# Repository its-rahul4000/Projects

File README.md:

# 📂 Rahul Kumar – Engineering & Research Projects

This repository contains a collection of **academic, internship, research, and personal projects** developed during my undergraduate studies in **Electrical Engineering at IIT Bombay**.

The projects span across multiple domains:

- Cybersecurity
- Embedded Systems
- Artificial Intelligence & Machine Learning
- Full-Stack Development
- Computer Architecture
- Analog Computing
- Energy Systems & Forecasting
- Data Analytics

Each project includes code, reports, simulations, documentation, and real-world engineering solutions developed through academic, research, and industry experience.

# 📁 Project Overview

## 🛡️ Cybersecurity Log Intelligence System

### Enterprise Security Log Analysis & Threat Detection Platform

- Architected and developed an **enterprise Cybersecurity Log Intelligence System** for automated security log analysis and threat detection.
- Implemented **static rule-based and behavioral anomaly detection** to identify attacks from large-scale log datasets.
- Built an interactive **dashboard with visualizations**, PDF/CSV report generation, and automated security insights.
- Designed a secure **RBAC-based application** featuring Argon2id authentication, audit logging, configurable detection rules, concurrent log processing, and secure data lifecycle management.
- Incorporated industry security frameworks including **MITRE ATT&CK, OWASP, NIST SP 800-53, ISO/IEC 27001, CERT-In, and the EU Cyber Resilience Act**.

### Key Features

- Multi-format log parsing and automated threat detection
- Static signature and behavioral anomaly detection
- Interactive Streamlit dashboard with security analytics
- PDF & CSV security report generation
- Configurable detection-rule management
- Role-Based Access Control (Administrator & IT Owner)
- Audit logging and secure session management
- Concurrent processing for large log files

### Technologies

- Python
- Streamlit
- SQLite
- Pandas
- Plotly
- Argon2id Authentication
- YAML Rule Engine
- MITRE ATT&CK
- OWASP

## 🏗️ Concrete Maturity Meter

### Embedded IoT System for Concrete Strength Monitoring

- Developed a **low-power embedded device** for real-time monitoring of concrete curing using temperature-based maturity models.  
- Implemented **on-device computation of maturity index and strength %** using MCU.  
- Integrated **TMP1075 sensor, SPI Flash, and BLE (CC2650)** for sensing, storage, and communication.  
- Designed a **battery-powered ultra-low power system** using sleep modes and duty-cycled BLE.  
- Enables **non-destructive, in-situ strength estimation**, eliminating traditional delays.  

### Key Highlights

- Sampling every **10–15 minutes with long battery life (>2 months)**  
- Reliable BLE communication **through concrete (≈ 8–9 cm range)** 
- Compact embedded system (~40×30×20 mm)  
- Full pipeline: sensing → storage → computation → wireless broadcast  

## 🌊 Forecasting of Offshore Wind Power

### Time-Series Forecasting & Renewable Energy Analysis

- Developed a **data-driven forecasting model** for offshore wind power generation.  
- Applied **time-series analysis and machine learning techniques** to predict power output.  
- Preprocessed real-world datasets including **wind speed, temporal patterns, and environmental factors**.  
- Built models to capture **seasonal trends, variability, and uncertainty in renewable energy systems**.  

### Key Contributions

- Data cleaning and feature engineering for time-series modeling  
- Implementation of forecasting models (statistical / ML-based)  
- Performance evaluation using error metrics (MAE, RMSE)  
- Visualization of predicted vs actual wind power trends  

### Impact

- Helps in **grid stability and energy planning**  
- Supports **renewable energy integration**

## 🧠 Integrated AI Query System

### AI-powered Knowledge Assistant

- Built an AI system capable of **answering, comparing, and summarizing queries**.  
- Used **Sentence Transformers (semantic search)** + rule-based parsing.  
- Implemented complete pipeline for:
  - Data cleaning  
  - Entity resolution  
  - Insight extraction  
- Developed interactive UI using **Streamlit**.

## 🌐 Full Stack Website Development

### Full-Stack Hardware Store Website

- Built a **complete e-commerce platform** with separate **user & admin portals**.  
- Backend: **Node.js, Express.js, MongoDB**  
- Frontend: **HTML, CSS, JavaScript (responsive design)**  

### Features

- Product browsing + **Featured & Hot Products**
- Cart & order system  
- Admin dashboard (products, orders, messages)  
- Customer–admin communication  

## 💻 Pipelined CPU

### 5-Stage Pipelined Processor (VHDL)

- Designed an **8-bit pipelined CPU** with:
  - IF, ID, EX, MEM, WB stages  
- Implemented:
  - Hazard detection  
  - Data forwarding  
  - Pipeline stalls  

## 🧮 Multicycle CPU

### 16-bit Multicycle Processor

- Designed CPU using **FSM-controlled datapath architecture**  
- Supported:
  - Arithmetic operations  
  - Branching  
  - Memory access  

## 🔌 Microcontrollers UART Communication

### 8051 Communication System

- Implemented **master-slave communication** using AT89C5131  
- Designed **full-duplex UART logic** with synchronization  
- Displayed outputs on **LCD modules**  

## 📡 Wireless Communication (GNU Radio)

- Designed a **complete digital communication system** using GNU Radio  
- Implemented:
  - ASK, FSK, PSK, QAM  
- Tested with **RTL-SDR hardware**  
- Analyzed performance under noise and synchronization errors

 ## 🧪 VHDL Project

### Digital Logic Design

- Designed multiple components:
  - ALU  
  - FSM  
  - Multiplexers  
  - Adders  

- Implemented on FPGA with timing validation   
## ⚡ Analog Computer

### Vertical Motion Analog Computing System

- Designed an **analog computer using op-amps** to solve differential equations.  
- Implemented **integrators, summers, buffers** for physical system modeling.  
- Simulated using **LTSpice** and validated experimentally. 

## 🔬 SOS (Summer of Science)

### AI & ML Theory Study

- Studied:
  - Regression models  
  - Optimization algorithms  
  - Neural networks  
  - PCA & clustering  

- Built strong theoretical foundation in ML  

## 📊 HS312 Project

### Sleep & Dream Quality Analysis

- Collected and analyzed personal sleep data  
- Performed:
  - Visualization  
  - Correlation analysis  
  - Behavioral insights  

## 📦 Data Analytics Project

### Logistics AI Platform Analysis

- Compared platforms: **Mojro, Locus, FarEye, LogiNext**  
- Evaluated:
  - AI capabilities  
  - Tech stack  
  - Market positioning  

# 📌 About Me

- **Rahul Kumar**
- +91-7050243955
- B.Tech, Electrical Engineering  
- Indian Institute of Technology Bombay  
- LinkedIn:https://www.linkedin.com/in/rahul-kumar-90186830a

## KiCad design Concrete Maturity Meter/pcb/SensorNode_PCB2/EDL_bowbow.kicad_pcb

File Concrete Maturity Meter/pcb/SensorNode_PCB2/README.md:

# Sensor Node PCB – Layout and Electrical Design

## Board Specifications

- Dimensions: 18.5 mm × 16 mm  
- Layers: 2-layer PCB  
- Stackup: Top (components + signals), Bottom (ground plane)  

---

## Layout Strategy

The sensor node PCB is designed for minimal footprint and simplicity, with all components placed to ensure short signal paths and stable operation.

### Placement considerations:
- Temperature sensor placed centrally to ensure uniform thermal exposure
- Pull-up resistors placed close to sensor pins
- Decoupling capacitor placed directly adjacent to sensor VDD pin
- Connector placed at board edge for straightforward interfacing

---

## Power Routing

- VDD routed directly from connector to sensor with minimal trace length
- Single decoupling capacitor used to stabilize supply
- Ground plane implemented on bottom layer for noise suppression

---

## Signal Routing

### I²C Lines (SDA, SCL)
- Routed as short traces between connector and sensor
- Avoided unnecessary vias to reduce impedance and noise
- Maintained consistent spacing between SDA and SCL

---

## Via Usage

- Minimal vias used due to small board size
- Only used where routing on top layer was not feasible
- Ground vias used to connect pads to ground plane

---

## Grounding Strategy

- Continuous ground plane on bottom layer
- Direct connection from sensor GND pin to ground plane
- Ensures stable reference for I²C communication

---

## Manufacturing Considerations

- Component sizes:
  - Resistors: 0805
  - Capacitors: 0603
- Layout optimized for hand soldering despite compact size
- Short trace lengths reduce susceptibility to noise

---

## Known PCB-Level Issues

- Very compact layout reduced routing flexibility
- Close spacing between components required careful soldering
- Limited mechanical robustness due to small board area
- No dedicated shielding or encapsulation provision on PCB

---

## Summary

The sensor node PCB is optimized for compactness and simplicity, focusing on reliable temperature sensing and stable I²C communication. The layout minimizes signal path lengths and ensures proper power decoupling within a constrained footprint.

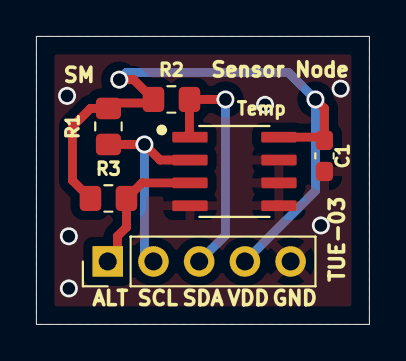
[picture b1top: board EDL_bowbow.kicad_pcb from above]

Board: 2 copper layers, 18.5 x 16.0 mm, 6 parts (0 on the bottom side), 5 nets.

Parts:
C1: 0.01u; C_0603_1608Metric_Pad1.08x0.95mm_HandSolder
R1, R2, R3: 5k; R_0805_2012Metric_Pad1.20x1.40mm_HandSolder
TEMPDB1: Conn_01x05_Pin; PinHeader_1x05_P2.54mm_Vertical
Temp: TMP1075DR; SOIC127P599X175-8N

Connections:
GND: C1.2, TEMPDB1.5, Temp.4 (GND), Temp.5 (A2), Temp.6 (A1), Temp.7 (AO)
unnamed: R3.2, TEMPDB1.1, Temp.3 (ALERT)
unnamed: R1.2, TEMPDB1.2, Temp.2 (SCL)
unnamed: R2.2, TEMPDB1.3, Temp.1 (SDA)
VDD: C1.1, R1.1, R2.1, R3.1, TEMPDB1.4, Temp.8 (V+)

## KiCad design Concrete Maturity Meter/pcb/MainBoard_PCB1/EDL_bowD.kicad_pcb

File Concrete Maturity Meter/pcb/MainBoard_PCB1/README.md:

# MainBoard PCB – Layout and Electrical Design

## Board Specifications

- Dimensions: 38.5 mm × 23.76 mm  
- Layers: 2-layer PCB  
- Stackup: Top (signal + components), Bottom (ground plane dominant)  

---

## Layout Strategy

The board is designed around a dense central module (CC2650MODA), with peripheral components arranged to minimize trace length and routing congestion.

### Placement considerations:
- BLE module placed near board edge to preserve antenna radiation
- Flash memory placed close to MCU pins to reduce SPI trace length
- LDO regulator positioned near battery input pads
- Decoupling capacitors placed within 2–3 mm of IC power pins
- JTAG header placed at edge for accessibility during debugging

---

## Power Routing

- Battery input routed directly to LDO input using wider traces (0.5 mm)
- 3.3V output distributed using short, low-impedance paths
- Ground plane implemented on bottom layer for:
  - return current path
  - noise reduction
- Local decoupling applied at:
  - MCU supply pins
  - flash memory supply

---

## Signal Routing

### I²C Lines (Sensor Interface)
- Routed as short parallel traces
- Pull-up resistors placed close to MCU side

### SPI Lines (Flash Memory)
- Routed with minimal length mismatch
- Avoided crossing splits in ground plane
- Kept away from high-current paths

---

## Via Usage

- Used for:
  - layer transitions during routing congestion
  - connecting top signals to bottom ground plane
- Typical via size:
  - Diameter: 1 mm

Vias are avoided near high-density pads to prevent DRC violations.

---

## Grounding Strategy

- Continuous ground plane on bottom layer
- Multiple stitching vias used to connect ground pads to plane
- Ground return paths kept short and uninterrupted

---

## Antenna Keepout (Critical)

- Region under BLE antenna kept completely free of:
  - copper
  - vias
  - traces
- No ground plane beneath antenna section

This is essential to maintain RF performance.

---

## Manufacturing Considerations

- Footprints selected considering hand soldering:
  - Resistors: 0603 / 0805
  - Capacitors: 0603 / 0805

---

## Known PCB-Level Issues

- Tight pad spacing within BLE module footprint caused DRC clearance violations
- Some pads inside module footprint required net reassignment to avoid false errors
- Dense routing near module required multiple vias, increasing layout complexity
- Small component sizes made manual assembly difficult

---

## Summary

The PCB design prioritizes compactness while maintaining signal integrity, stable power delivery, and RF performance. Layout decisions were driven by the constraints imposed by the BLE module and the need for reliable operation in a small form factor.

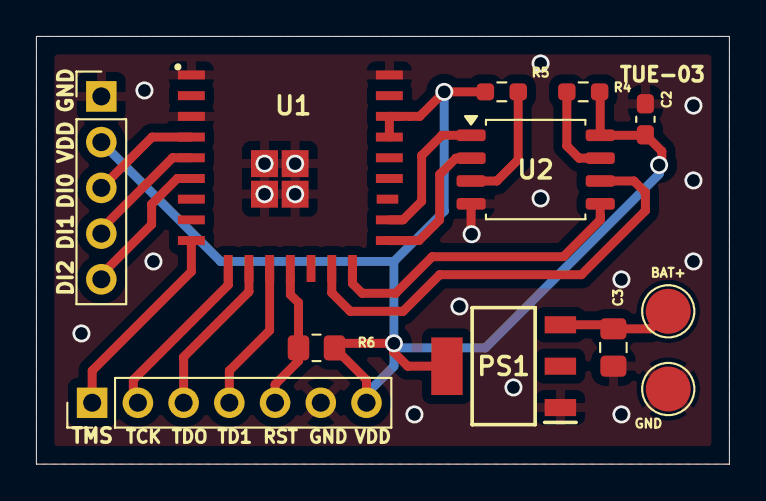
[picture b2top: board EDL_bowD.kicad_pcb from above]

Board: 2 copper layers, 38.5 x 23.8 mm, 12 parts (0 on the bottom side), 17 nets.

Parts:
BAT+: BAT; TestPoint_Pad_D2.5mm
C2: 0.1u; C_0603_1608Metric_Pad1.08x0.95mm_HandSolder
C3: 1u; C_0805_2012Metric_Pad1.18x1.45mm_HandSolder
Code1: Conn_01x07_Pin; PinHeader_1x07_P2.54mm_Vertical
GND: GND; TestPoint_Pad_D2.5mm
PS1: TC2117-3.3VDBTR; SOT230P700X180-4N
R4, R5: 3.3k; R_0603_1608Metric_Pad0.98x0.95mm_HandSolder
R6: 100k; R_0805_2012Metric_Pad1.20x1.40mm_HandSolder
TEMPMB1: Conn_01x05_Pin; PinHeader_1x05_P2.54mm_Vertical
U1: CC2650MODAMOHR; XCVR_CC2650MODAMOHR
U2: W25Q32JVSSIQ; SOIC-8_5.3x5.3mm_P1.27mm

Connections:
GND: C2.2, C3.2, Code1.6, GND.1, PS1.1 (GND), TEMPMB1.1, U1.1 (GND), U1.3 (GND), U1.25 (GND), U1.26 (EGP), U1.27 (EGP), U1.28 (EGP), U1.29 (EGP), U2.4 (GND)
unnamed: Code1.1, U1.9 (JTAG_TMS)
unnamed: Code1.2, U1.10 (JTAG_TCK)
unnamed: Code1.3, U1.11 (DIO_5/JTAG_TDO)
unnamed: Code1.4, U1.12 (DIO_6/JTAG_TDI)
unnamed: Code1.5, R6.2, U1.13 (~RESET)
unnamed: BAT+.1, C3.1, PS1.3 (VIN)
unnamed: TEMPMB1.3, U1.4 (DIO_0)
unnamed: TEMPMB1.4, U1.5 (DIO_1)
unnamed: TEMPMB1.5, U1.6 (DIO_2)
unnamed: U1.15 (DIO_8), U2.6 (CLK)
unnamed: U1.16 (DIO_9), U2.5 (DI(IO0))
unnamed: U1.17 (DIO_10), U2.2 (DO(IO1))
unnamed: U1.18 (DIO_11), U2.1 (~CS)
unnamed: R4.1, U2.7 (~HOLD/~RESET(IO3))
unnamed: R5.1, U2.3 (~WP(IO2))
VDD: C2.1, Code1.7, PS1.4 (VOUT_2), R4.2, R5.2, R6.1, TEMPMB1.2, U1.22 (VDD), U1.23 (VDD), U2.8 (VCC)

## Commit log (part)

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2025-10-19 Update README to describe repository contents
2025-10-19 Fix capitalization in README description
2025-12-27 Full Stack Website
2026-03-10 Update project description in README
2026-03-11 Revise README with project details and contact info
    Updated README to include project descriptions, technologies used, and personal information.
2026-03-11 Rename Assignment_Rahul_Kumar.xlsx to Excel_Report
2026-03-11 Update project title to include 'Humanity Science'
2026-04-15 uploaded the all relevant file
2026-04-15 new project added
2026-04-15 new project uploaded
2026-04-15 Update README with note on testing code
    Added a note about additional testing code in the source directory.
2026-04-17 Award section added
2026-04-29 changed
2026-06-11 11-06-2026
2026-06-13 Delete Cybersecurity Log Intelligence System directory
    update
